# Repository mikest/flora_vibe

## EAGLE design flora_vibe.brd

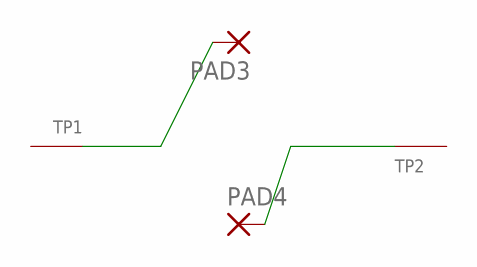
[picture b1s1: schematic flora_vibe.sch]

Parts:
PAD3, PAD4: 2,54/1,0
TP1, TP2: SEWTAP0.4IN; SEWINGTAP_0.4

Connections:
unnamed: PAD3.1, TP1.TAP
unnamed: PAD4.1, TP2.TAP

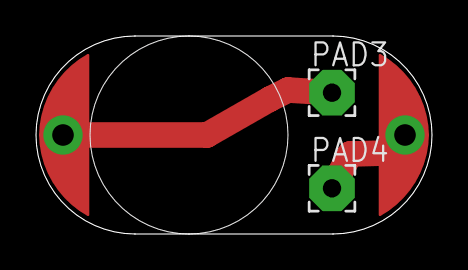
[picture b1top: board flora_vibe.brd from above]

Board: 2 copper layers, 22.0 x 11.0 mm, 4 parts (0 on the bottom side), 2 nets.

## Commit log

2013-05-02 initial checkin.
